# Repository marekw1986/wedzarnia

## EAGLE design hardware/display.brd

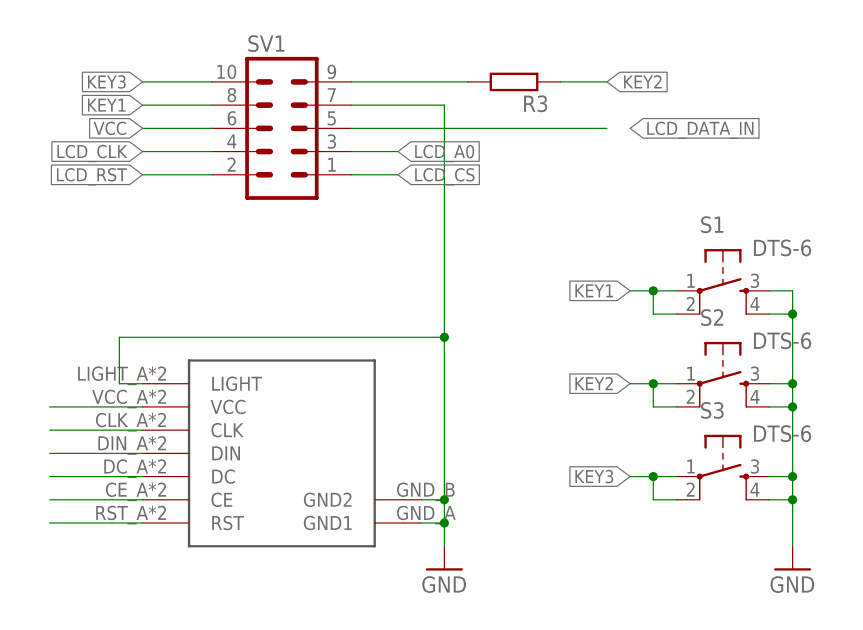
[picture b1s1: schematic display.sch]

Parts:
R3: R-EU_R2010; R2010
S1, S2, S3: DTS-6
SV1: ML10L
U$2: NOKIA5110_LCD

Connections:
GND: S1.3, S1.4, S2.3, S2.4, S3.3, S3.4, SV1.7, U$2.GND_A (GND1), U$2.GND_B (GND2), U$2.LIGHT_A (LIGHT), U$2.LIGHT_B (LIGHT)
KEY1: S1.1, S1.2, SV1.8
KEY2: R3.1, S2.1, S2.2
KEY3: S3.1, S3.2, SV1.10
LCD_A0: SV1.3, U$2.DC_A (DC), U$2.DC_B (DC)
LCD_CLK: SV1.4, U$2.CLK_A (CLK), U$2.CLK_B (CLK)
LCD_CS: SV1.1, U$2.CE_A (CE), U$2.CE_B (CE)
LCD_DATA_IN: SV1.5, U$2.DIN_A (DIN), U$2.DIN_B (DIN)
LCD_RST: SV1.2, U$2.RST_A (RST), U$2.RST_B (RST)
unnamed: R3.2, SV1.9
VCC: SV1.6, U$2.VCC_A (VCC), U$2.VCC_B (VCC)

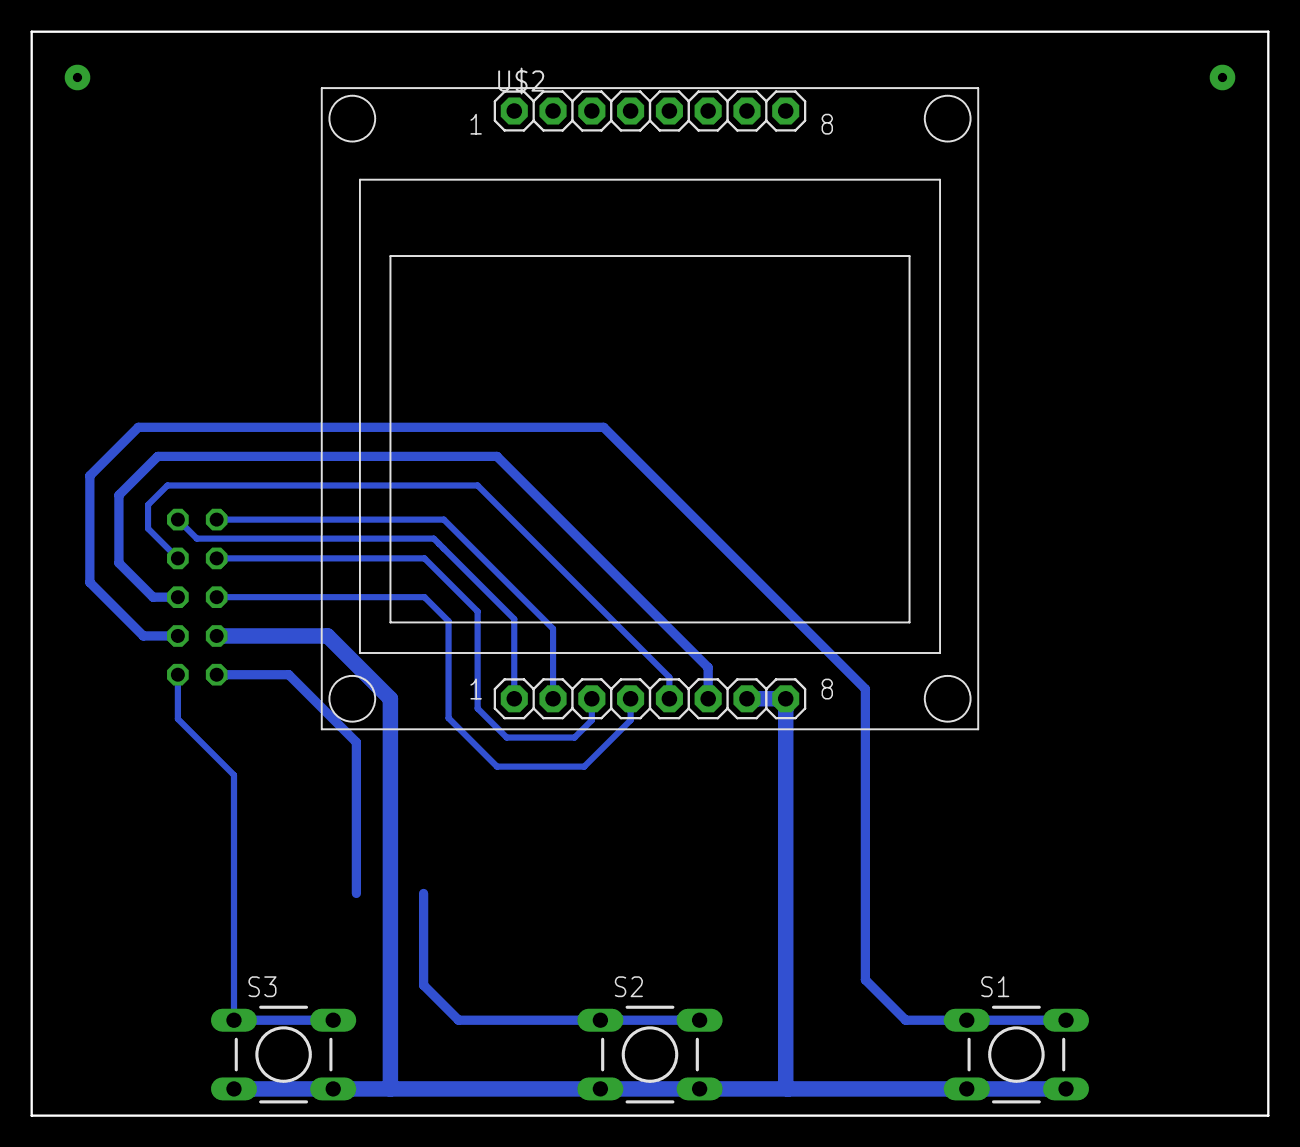
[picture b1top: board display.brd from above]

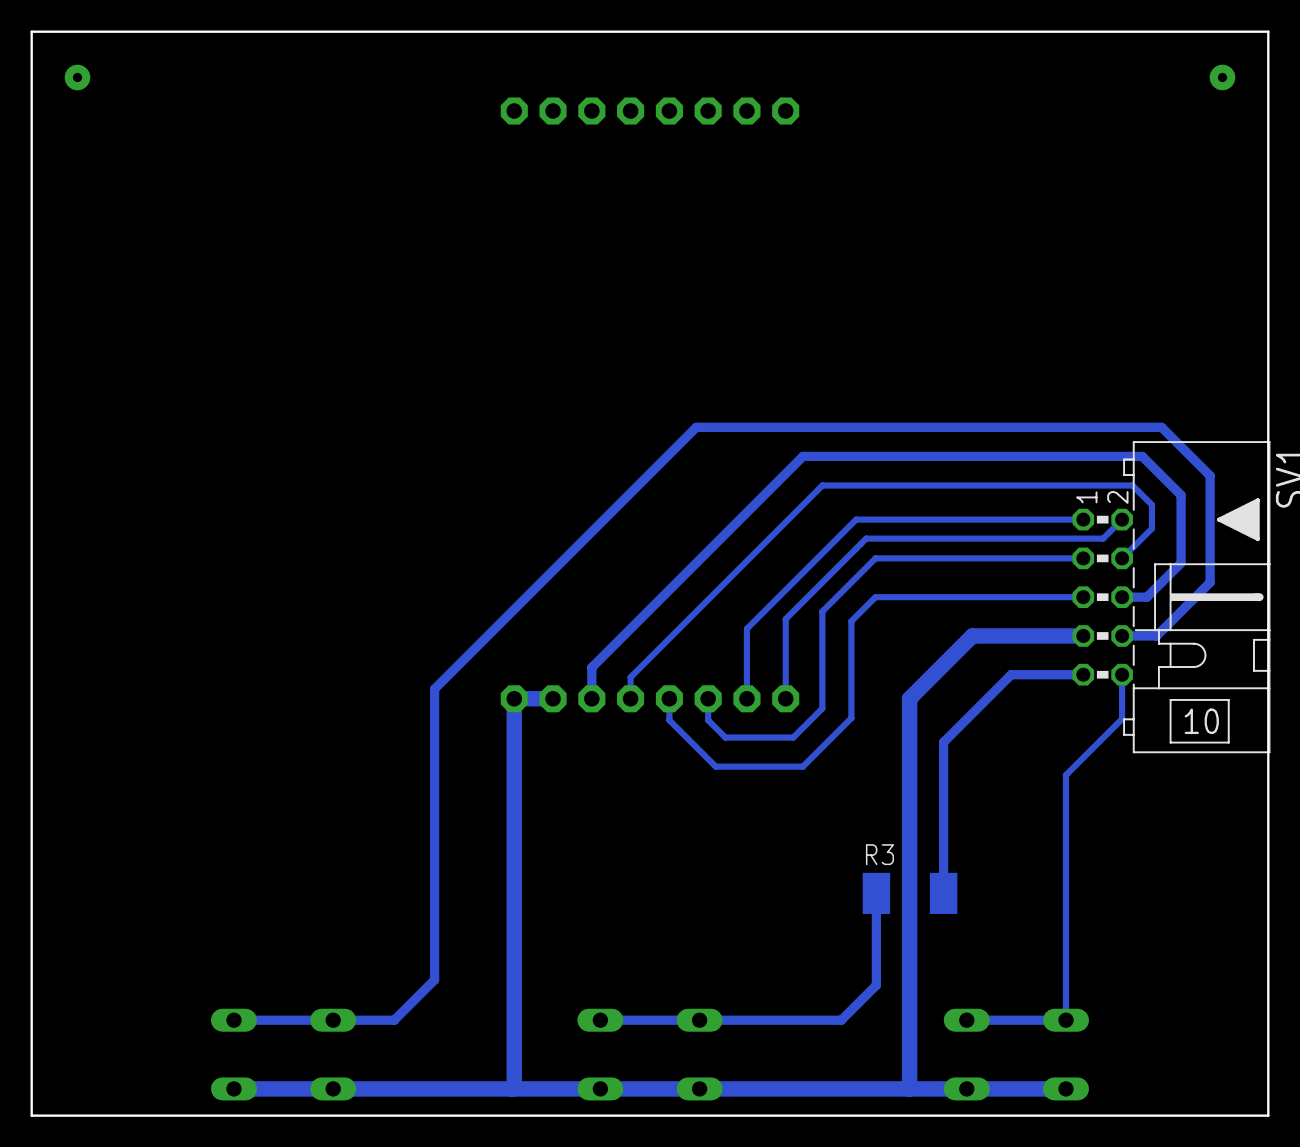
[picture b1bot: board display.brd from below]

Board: 2 copper layers, 81.0 x 71.0 mm, 6 parts (2 on the bottom side), 11 nets.

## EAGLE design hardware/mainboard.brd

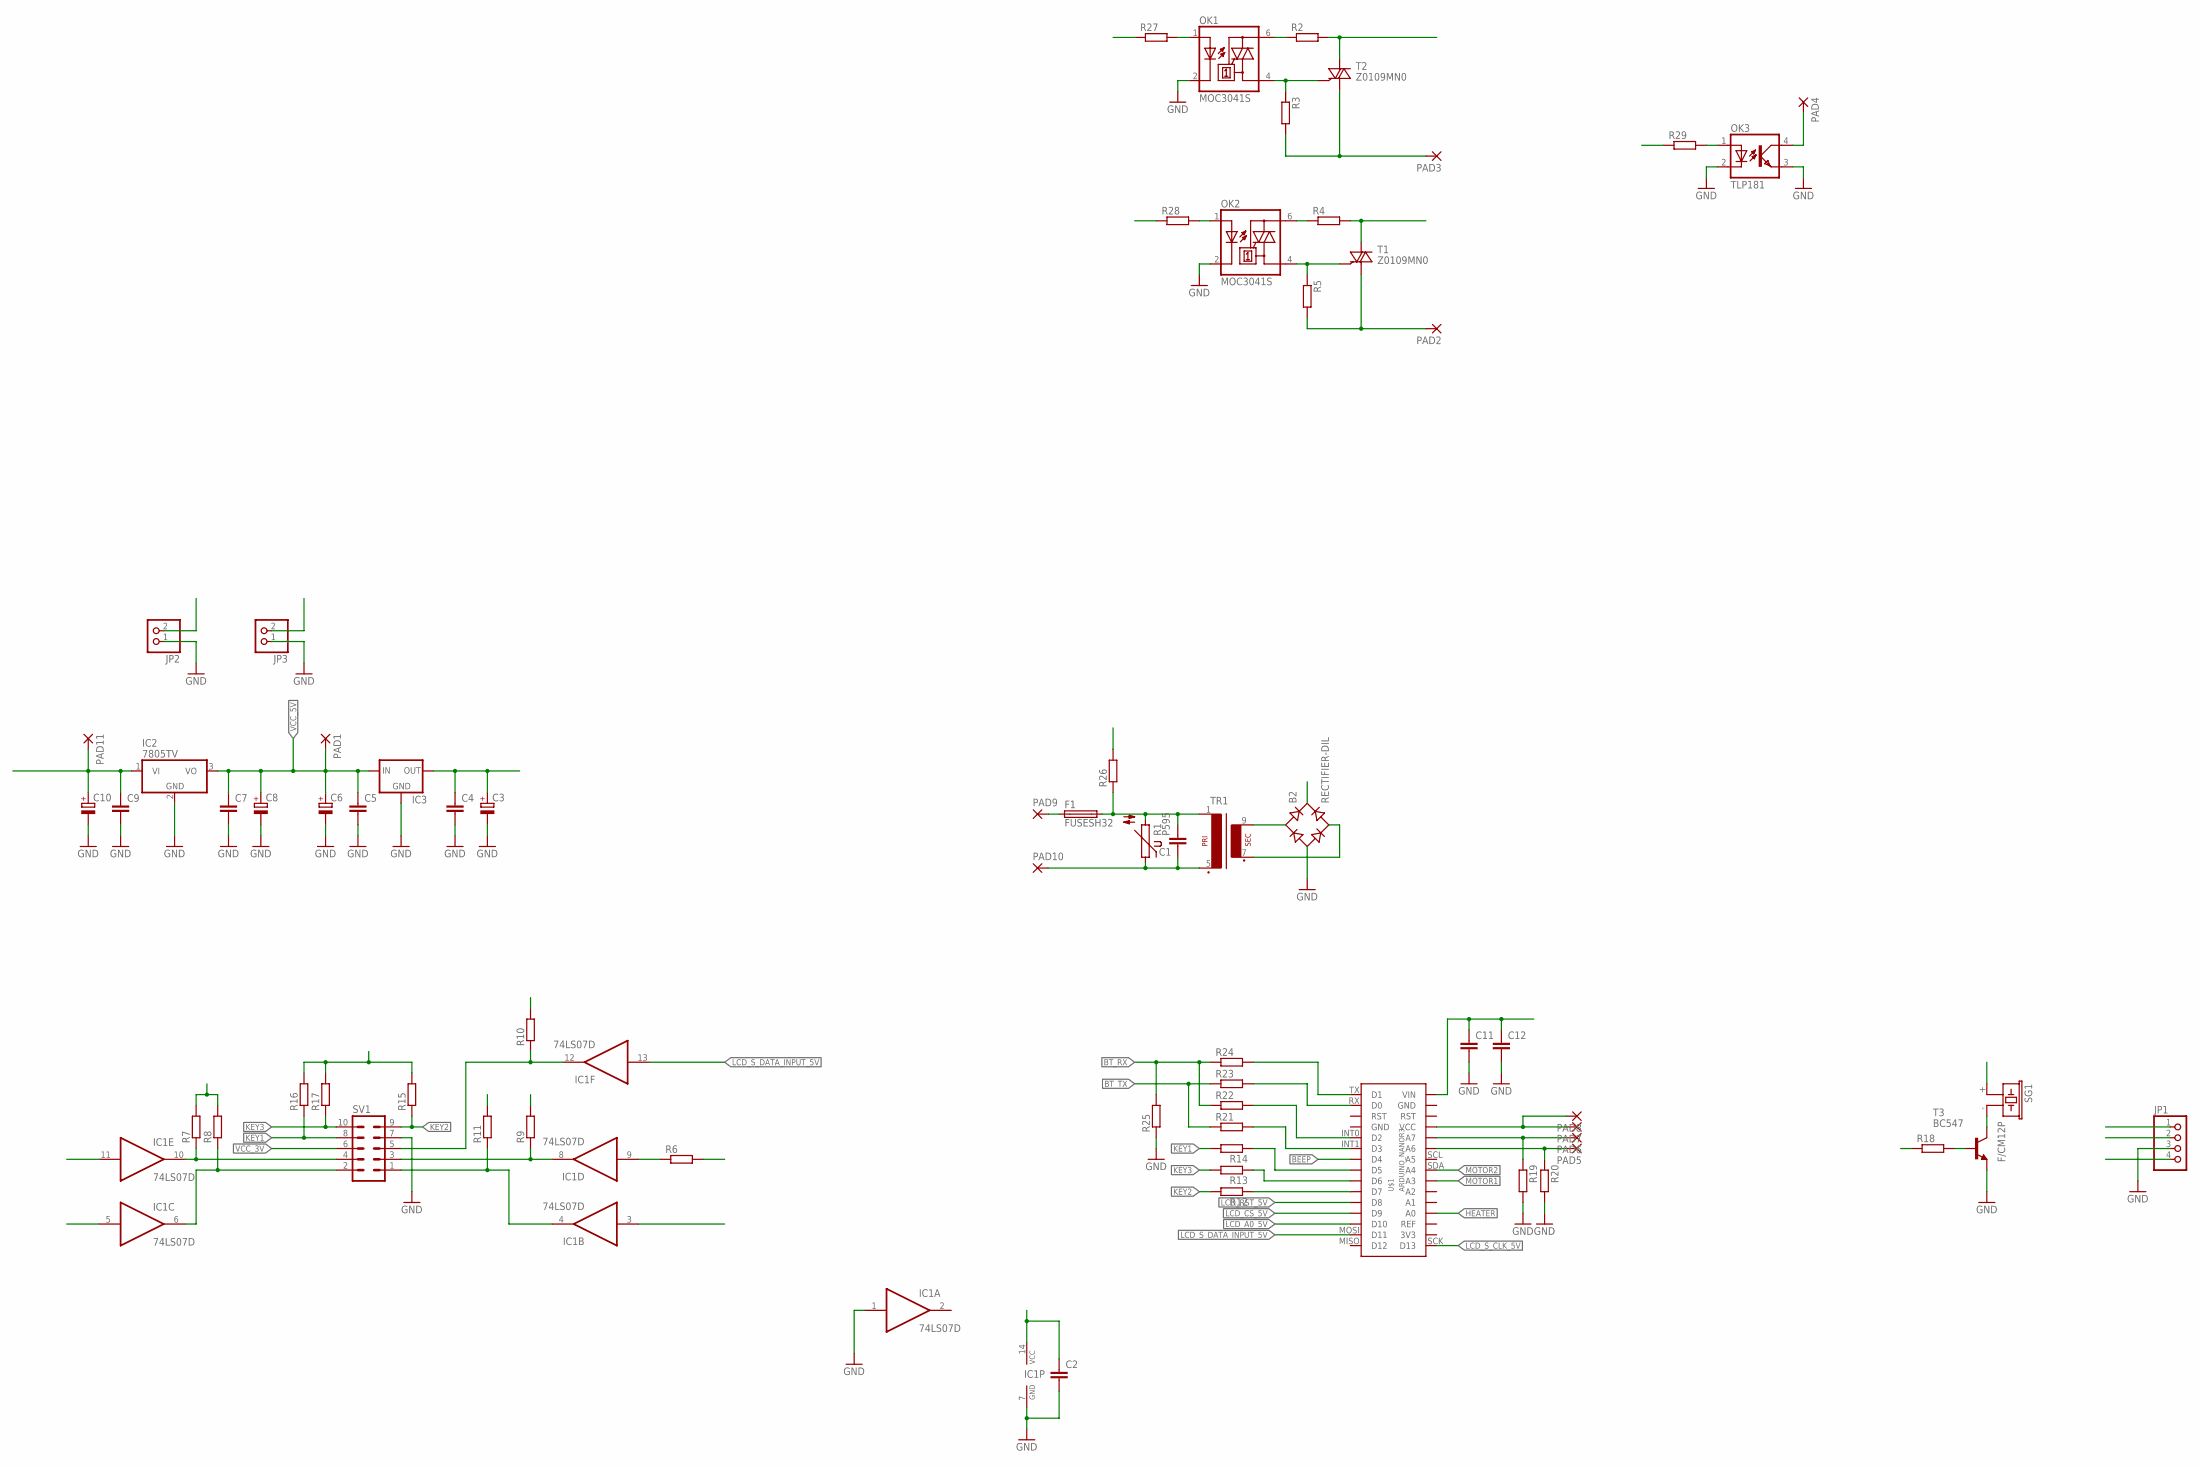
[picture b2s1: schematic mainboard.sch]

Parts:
B2: RECTIFIER-DIL; B-DIL
C1: C-EU150-054X183; C150-054X183
C2, C7, C9, C11, C12: C-EUC1206; C1206
C3, C6: CPOL-EUSMCB; SMC_B
C4, C5: C-EUC0603; C0603
C8: CPOL-EUSMCC; SMC_C
C10: CPOL-EU150CLZ-0810; 150CLZ-0810
F1: FUSESH32; SH32
IC1: 74LS07D; SO14
IC2: 7805TV; TO220V
IC3: 78XXS
JP1: PINHD-1X4; 1X04
JP2, JP3: PINHD-1X2; 1X02
OK1, OK2: MOC3041S; DIL6-SMD
OK3: TLP181; SO-4
PAD1, PAD2, PAD3, PAD4, PAD5, PAD6, PAD7, PAD8, PAD11: 2,54/1,1
PAD9, PAD10: 3,81/1,4
R1: P595
R2, R3, R4, R5: R-EU_R1206; R1206
R6, R7, R8, R11, R15, R16, R17, R21, R22, R23, R24, R25, R29: R-EU_R0603; R0603
R9, R19, R20, R28: R-EU_0204/5; 0204/5
R10, R12, R13, R14, R27: R-EU_0204/7; 0204/7
R18: R-EU_0207/10; 0207/10
R26: R-EU_VTA53; VTA53
SG1: F/CM12P
SV1: ML10
T1, T2: Z0109MN0; SOT223
T3: BC547; TO92
TR1: EI30-1
U$1: ARDUINO_NANOR3; ARDUINO-NANO

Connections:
3V3: U$1.3V3
BEEP: R18.1, U$1.D4
BT_RX: JP1.1, R22.1, R24.1, R25.2
BT_TX: JP1.2, R21.1, R23.1
G: OK2.4 (A1), R5.1, T1.3 (G)
GND: B2.-, C2.2, C3.-, C4.2, C5.2, C6.-, C7.2, C8.-, C9.2, C10.-, C11.2, C12.2, IC1.1 (I), IC1.7 (GND), IC2.2 (GND), IC3.GND, JP1.3, JP2.1, JP3.1, OK1.2 (C), OK2.2 (C), OK3.2 (C), OK3.3 (EMIT), R19.2, R20.2, R25.1, SV1.7, T3.1 (E), U$1.GND@1 (GND), U$1.GND@2 (GND)
HEATER: R29.1, U$1.A0
KEY1: R14.2, R16.1, SV1.8
KEY2: R12.2, R15.1, SV1.9
KEY3: R13.2, R17.1, SV1.10
LCD_A0: IC1.8 (O), R9.1, SV1.3
LCD_A0_5V: R6.2, U$1.D10
LCD_CS_3V: IC1.4 (O), R11.1, SV1.1
LCD_CS_5V: IC1.3 (I), U$1.D9
LCD_RST_3V: IC1.6 (O), R8.1, SV1.2
LCD_RST_5V: IC1.5 (I), U$1.D8
LCD_S_CLK: IC1.10 (O), R7.1, SV1.4
LCD_S_CLK_5V: IC1.11 (I), U$1.SCK (D13)
LCD_S_DATA_INPUT: IC1.12 (O), R10.1, SV1.5
LCD_S_DATA_INPUT_5V: IC1.13 (I), U$1.MOSI (D11)
MOTOR1: R27.1, U$1.A3
MOTOR2: R28.1, U$1.SDA (A4)
unnamed: C1.1, PAD10.1, R1.1, TR1.5 (P2)
unnamed: C1.2, F1.2A (2), R1.2, R26.1, TR1.1
unnamed: B2.AC1, TR1.9 (S4)
unnamed: B2.AC2, TR1.7 (S3)
unnamed: OK1.6 (A2), R2.1
unnamed: OK1.4 (A1), R3.1, T2.3 (G)
unnamed: OK2.6 (A2), R4.1
unnamed: R21.2, U$1.INT1 (D3)
unnamed: F1.1A (1), PAD9.1
unnamed: IC1.9 (I), R6.1
unnamed: R12.1, U$1.D7
unnamed: R13.1, U$1.D6
unnamed: R14.1, U$1.D5
unnamed: PAD5.1, R20.1, U$1.A6
unnamed: PAD6.1, R19.1, U$1.A7
unnamed: R22.2, U$1.INT0 (D2)
unnamed: R23.2, U$1.RX (D0)
unnamed: R24.2, U$1.TX (D1)
unnamed: SG1.- (2), T3.3 (C)
unnamed: R18.2, T3.2 (B)
unnamed: OK1.1 (A), R27.2
unnamed: OK2.1 (A), R28.2
unnamed: OK3.1 (A), R29.2
unnamed: OK3.4 (COL), PAD4.1
unnamed: PAD2.1, R5.2, T1.2 (CM), T1.4 (CM)
unnamed: PAD3.1, R3.2, T2.2 (CM), T2.4 (CM)
VCC_3V: C3.+, C4.1, IC3.OUT, R7.2, R8.2, R9.2, R10.2, R11.2, SV1.6
VCC_5V: C5.1, C6.+, C7.1, C8.+, IC2.3 (VO), IC3.IN, JP1.4, JP2.2, PAD1.1, R15.2, R16.2, R17.2, SG1.+ (1)
VCC_5V_ARDUINO: C2.1, IC1.14 (VCC), PAD7.1, PAD8.1, U$1.VCC
VIN: B2.+, C9.1, C10.+, C11.1, C12.1, IC2.1 (VI), JP3.2, PAD11.1, U$1.VIN
WN: R2.2, R4.2, R26.2, T1.1 (LD), T2.1 (LD)

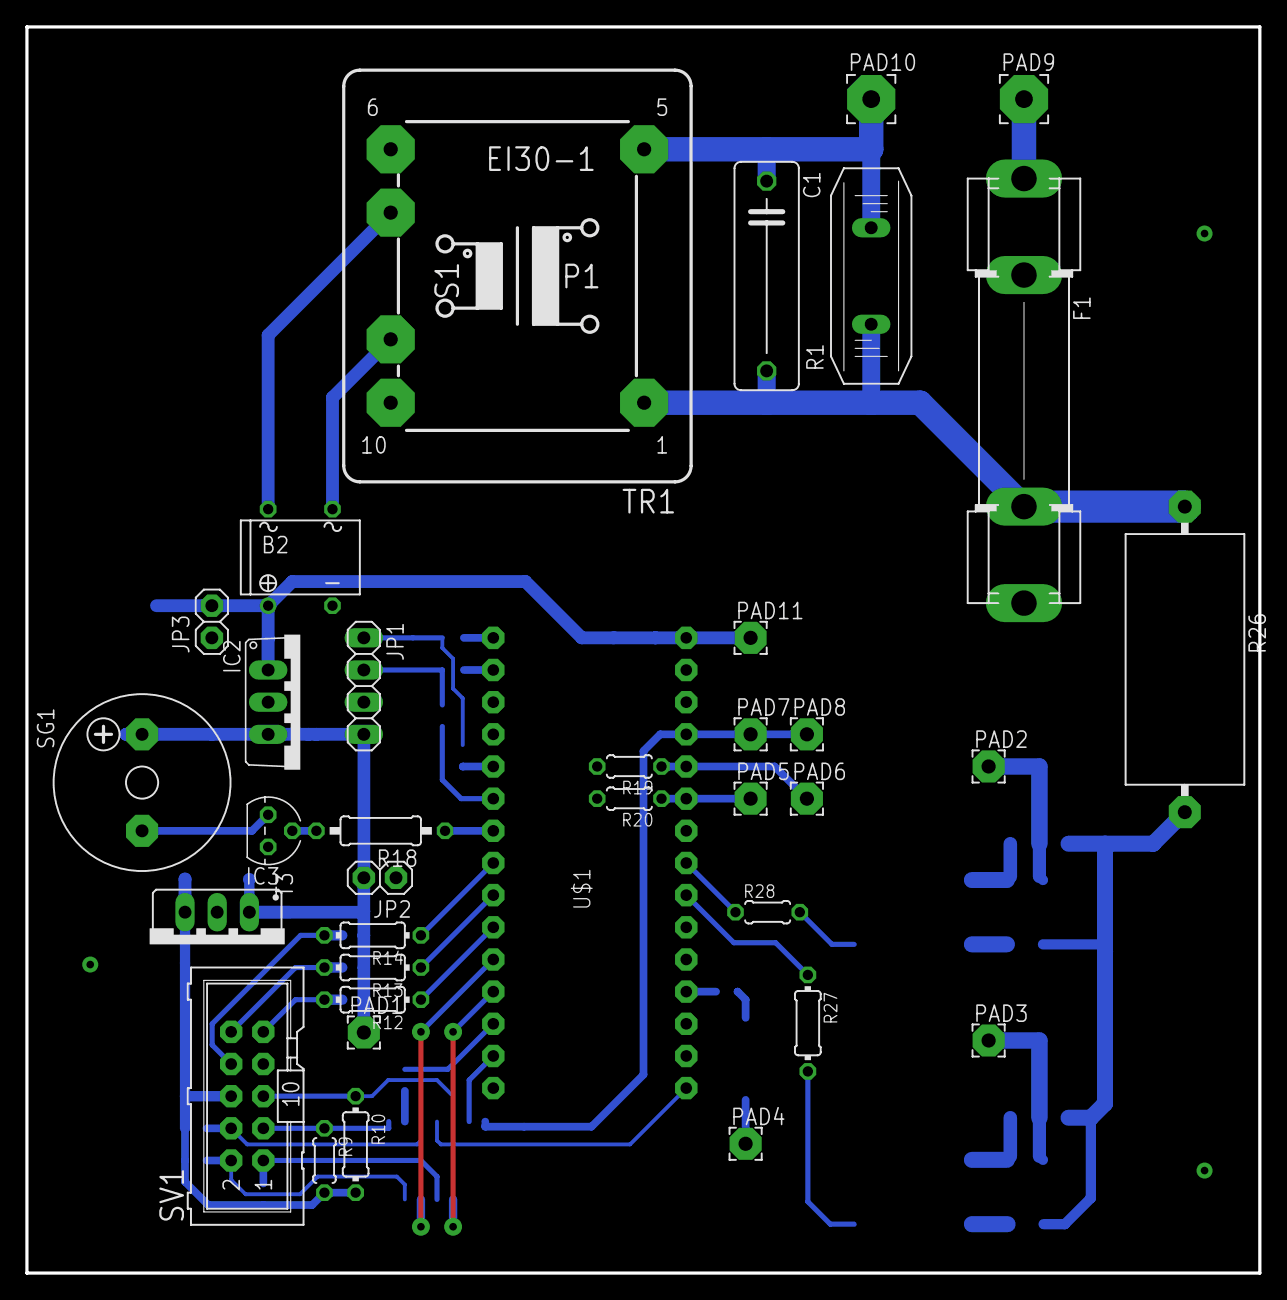
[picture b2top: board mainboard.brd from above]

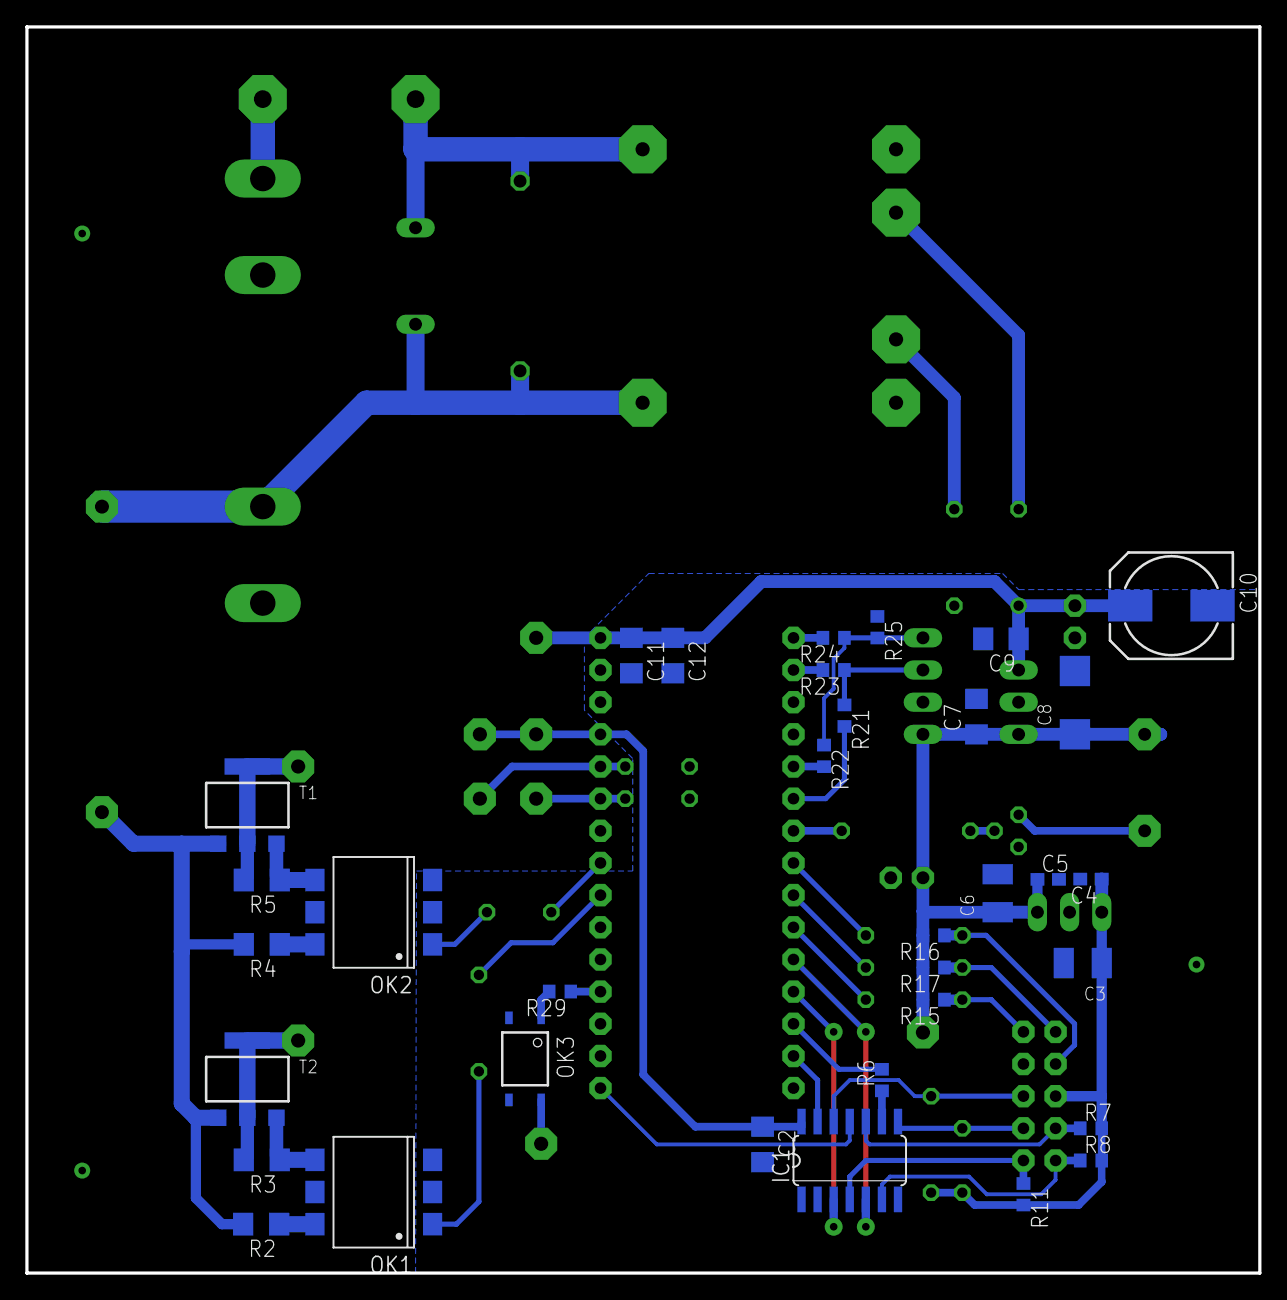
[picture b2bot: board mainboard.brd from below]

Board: 2 copper layers, 97.4 x 98.4 mm, 70 parts (34 on the bottom side), 52 nets.

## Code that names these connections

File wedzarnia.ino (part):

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#define LEFT_BUTTON_PIN     5
#define RIGHT_BUTTON_PIN    6
#define CENTRAL_BUTTON_PIN  7
#define BEEP_PIN            4
#define WIATRAK_PIN          17
#define POMPA_PIN          18

#define TEMP0_PIN           6
#define TEMP1_PIN           7

#define BT_TX_PIN           2
#define BT_RX_PIN           3

#define LCD_RST             8
#define LCD_CS              9
#define LCD_A0              10
#define LCD_DATA_IN         11
#define LCD_CLK             13


conf_t cfg;
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

void setup() {
  pinMode(BEEP_PIN, OUTPUT);
  digitalWrite(BEEP_PIN, 0);
  pinMode(WIATRAK_PIN, OUTPUT);
  digitalWrite(WIATRAK_PIN, 0);
  pinMode(POMPA_PIN, OUTPUT);
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        current_stage++;
        sekundy = 0;
        sekundy_do_konca = cfg.stage[current_stage].czas_trwania*60;
        digitalWrite(BEEP_PIN, 1);
        delay(300);
        restart_motor_cycle(&pompa_timer, POMPA_PIN, cfg.stage[current_stage].interwal_pompy);
        restart_motor_cycle(&wiatrak_timer, WIATRAK_PIN, cfg.stage[current_stage].interwal_wiatraka);
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            state = SELECT_PROGRAM;
            delay(1200);
        }
        digitalWrite(BEEP_PIN, 0);
      }

      handle_motor_cycle(&pompa_timer, POMPA_PIN, cfg.stage[current_stage].interwal_pompy*60000, cfg.stage[current_stage].praca_pompy*60000);
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            state = WEDZENIE_PERFORM;
            current_stage++;
             cfg.stage[current_stage].czas_trwania*60;
            digitalWrite(BEEP_PIN, 1);
            delay(300);
            restart_motor_cycle(&pompa_timer, POMPA_PIN, cfg.stage[current_stage].interwal_pompy);
            restart_motor_cycle(&wiatrak_timer, WIATRAK_PIN, cfg.stage[current_stage].interwal_wiatraka);            
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              sekundy = 0;
              delay(1200);
            }
            digitalWrite(BEEP_PIN, 0);
          }
        }
      }
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      //koncowa temperatura miesa zostala osiagnieta, zamykamy proces
      stop_all();
      state = SELECT_PROGRAM;
      digitalWrite(BEEP_PIN, 1);
      delay(1500);
      digitalWrite(BEEP_PIN, 0);
    }

    if ((unsigned long)(millis()-timer) >= 1000) {
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
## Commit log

2020-09-22 PCB added
